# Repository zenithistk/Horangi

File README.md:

# Horangi

The Horangi is a split ergonomic keyboard with a row-staggered and curved layout.

* [horangi](/horangi) - Reversible with integrated trackball
* [horangi_grin](/horangi_grin) - Fully wireless and grin layout

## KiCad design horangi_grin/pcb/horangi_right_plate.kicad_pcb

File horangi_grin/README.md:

# Horangi_grin

The 'Horangi_grin' keyboard is a fully wireless, ergonomic split keyboard. Inspired by the [Grin layout keyboard](https://kbd.news/Grin-layout-1348.html), this keyboard features a layout similar to a 75% keyboard, making it easy for users accustomed to standard keyboards to adapt to a split keyboard. It can be used separately for each hand or combined as needed, and is designed to be as compact as possible, ensuring both practicality and portability.

* 83-key keyboard, grin layout
* XIAO ble MCU
* Fully wireless
* Hot-swap

## Build Guide (WIP)
* [Build Guide](BUILDGUIDE.md)

## Firmware
Only zmk firmware is available.
* [zmk firmware](firmware)
* [source code](https://github.com/zenithistk/zmk-config-horangi_grin)

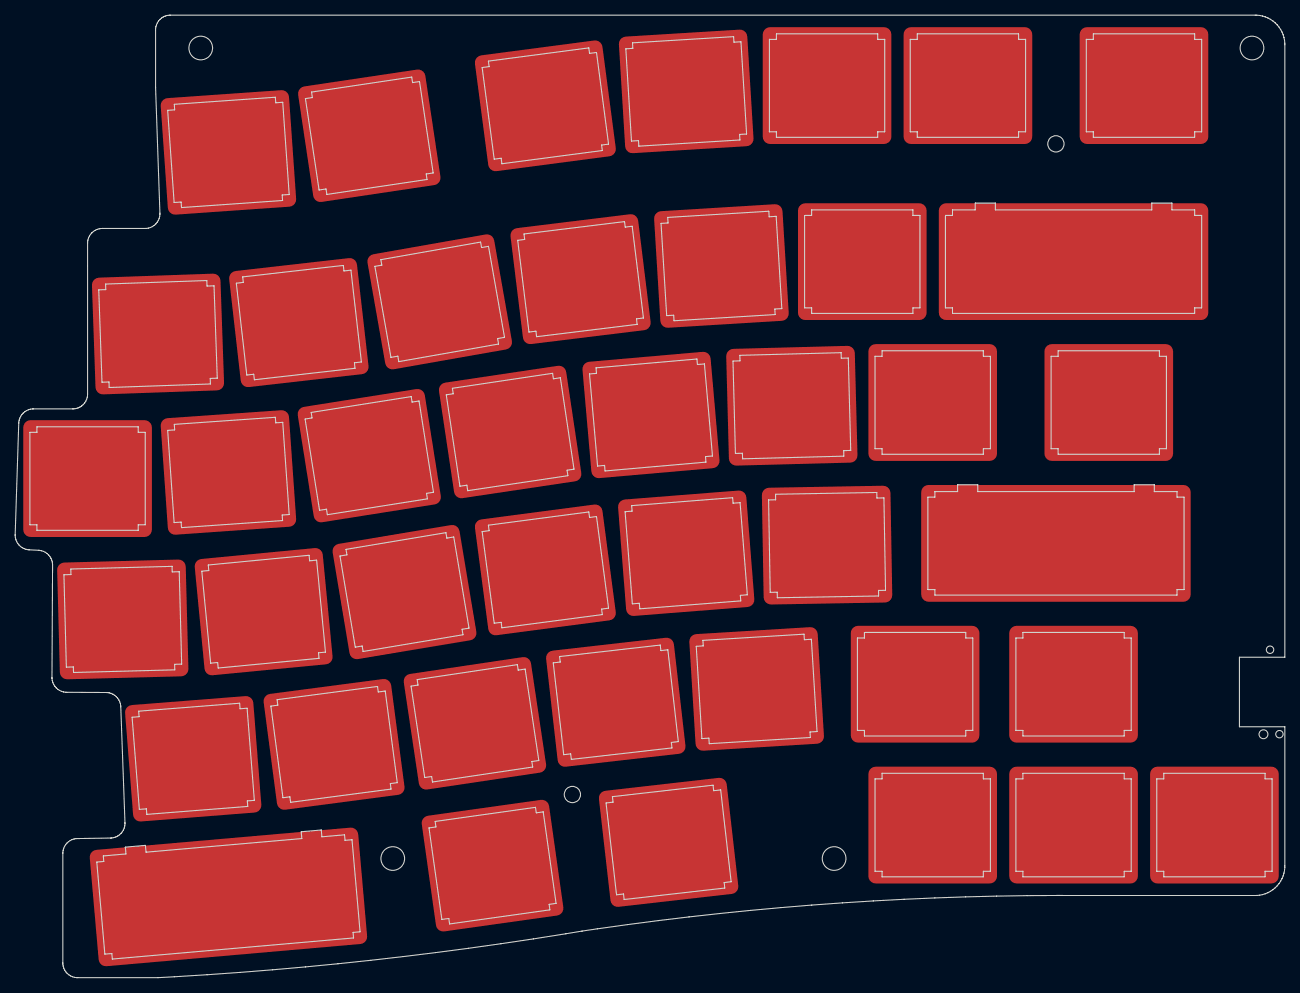
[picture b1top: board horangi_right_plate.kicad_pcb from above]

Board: 2 copper layers, 171.7 x 130.2 mm, 42 parts (0 on the bottom side), 7 nets, no tracks yet.

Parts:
SW1, SW2, SW3, SW4, SW5, SW6, SW7, SW8, SW9, SW10, SW11, SW12, SW13, SW15, SW16, SW17, SW18, SW19, SW20, SW21, SW22, SW23, SW24, SW25, SW26, SW27, SW28, SW29, SW30, SW31, SW32, SW33, SW34, SW37, SW38, SW39, SW40, SW41, SW42: Switch; MX-Alps_Switch_Cutout
SW14, SW35, SW36: Switch; MX-Alps_Switch_Cutout-1u_2u

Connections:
COL0: SW1.1 (COL), SW8.1 (COL), SW15.1 (COL), SW22.1 (COL), SW29.1 (COL), SW36.1 (COL)
COL1: SW2.1 (COL), SW9.1 (COL), SW16.1 (COL), SW23.1 (COL), SW30.1 (COL), SW37.1 (COL)
COL2: SW3.1 (COL), SW10.1 (COL), SW17.1 (COL), SW24.1 (COL), SW31.1 (COL), SW38.1 (COL)
COL3: SW4.1 (COL), SW11.1 (COL), SW18.1 (COL), SW25.1 (COL), SW32.1 (COL), SW39.1 (COL)
COL4: SW5.1 (COL), SW12.1 (COL), SW19.1 (COL), SW26.1 (COL), SW33.1 (COL), SW40.1 (COL)
COL5: SW6.1 (COL), SW13.1 (COL), SW20.1 (COL), SW27.1 (COL), SW34.1 (COL), SW41.1 (COL)
COL6: SW7.1 (COL), SW14.1 (COL), SW21.1 (COL), SW28.1 (COL), SW35.1 (COL), SW42.1 (COL)

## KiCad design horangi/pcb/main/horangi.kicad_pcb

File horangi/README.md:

# Horangi

The 'Horangi' keyboard is an ergonomic, symmetrical split keyboard with a built-in trackball. It utilizes Gateron KS-33 low profile switches and offers the option of hot-swapping. The MCU used is an rp2040 zero, contributing to a relatively small and aesthetically pleasing design. Additionally, it features m2 holes for tenting and supports the use of a trackball with additional parts.

Additionally, the Horangi features a very unique thumb cluster. It can be attached or detached as needed, and thanks to this special thumb cluster, it allows for the use of arrow keys, which are usually hard to find on typical split keyboards.

* 66-key layout, curved row stagger, arrow keys.
* rp2040-zero MCU
* Gateron low profile hot-swap
* Reversible pcb design
* Detachable thumb cluster
* Integrated trackball

## Keymap

## Build Guide (WIP)
* [Build Guide](BUILDGUIDE.md)

## Firmware
Only qmk firmware is available.
* [qmk firmware](firmware)
* [source code](https://github.com/zenithistk/qmk_firmware/tree/master/keyboards/horangi)

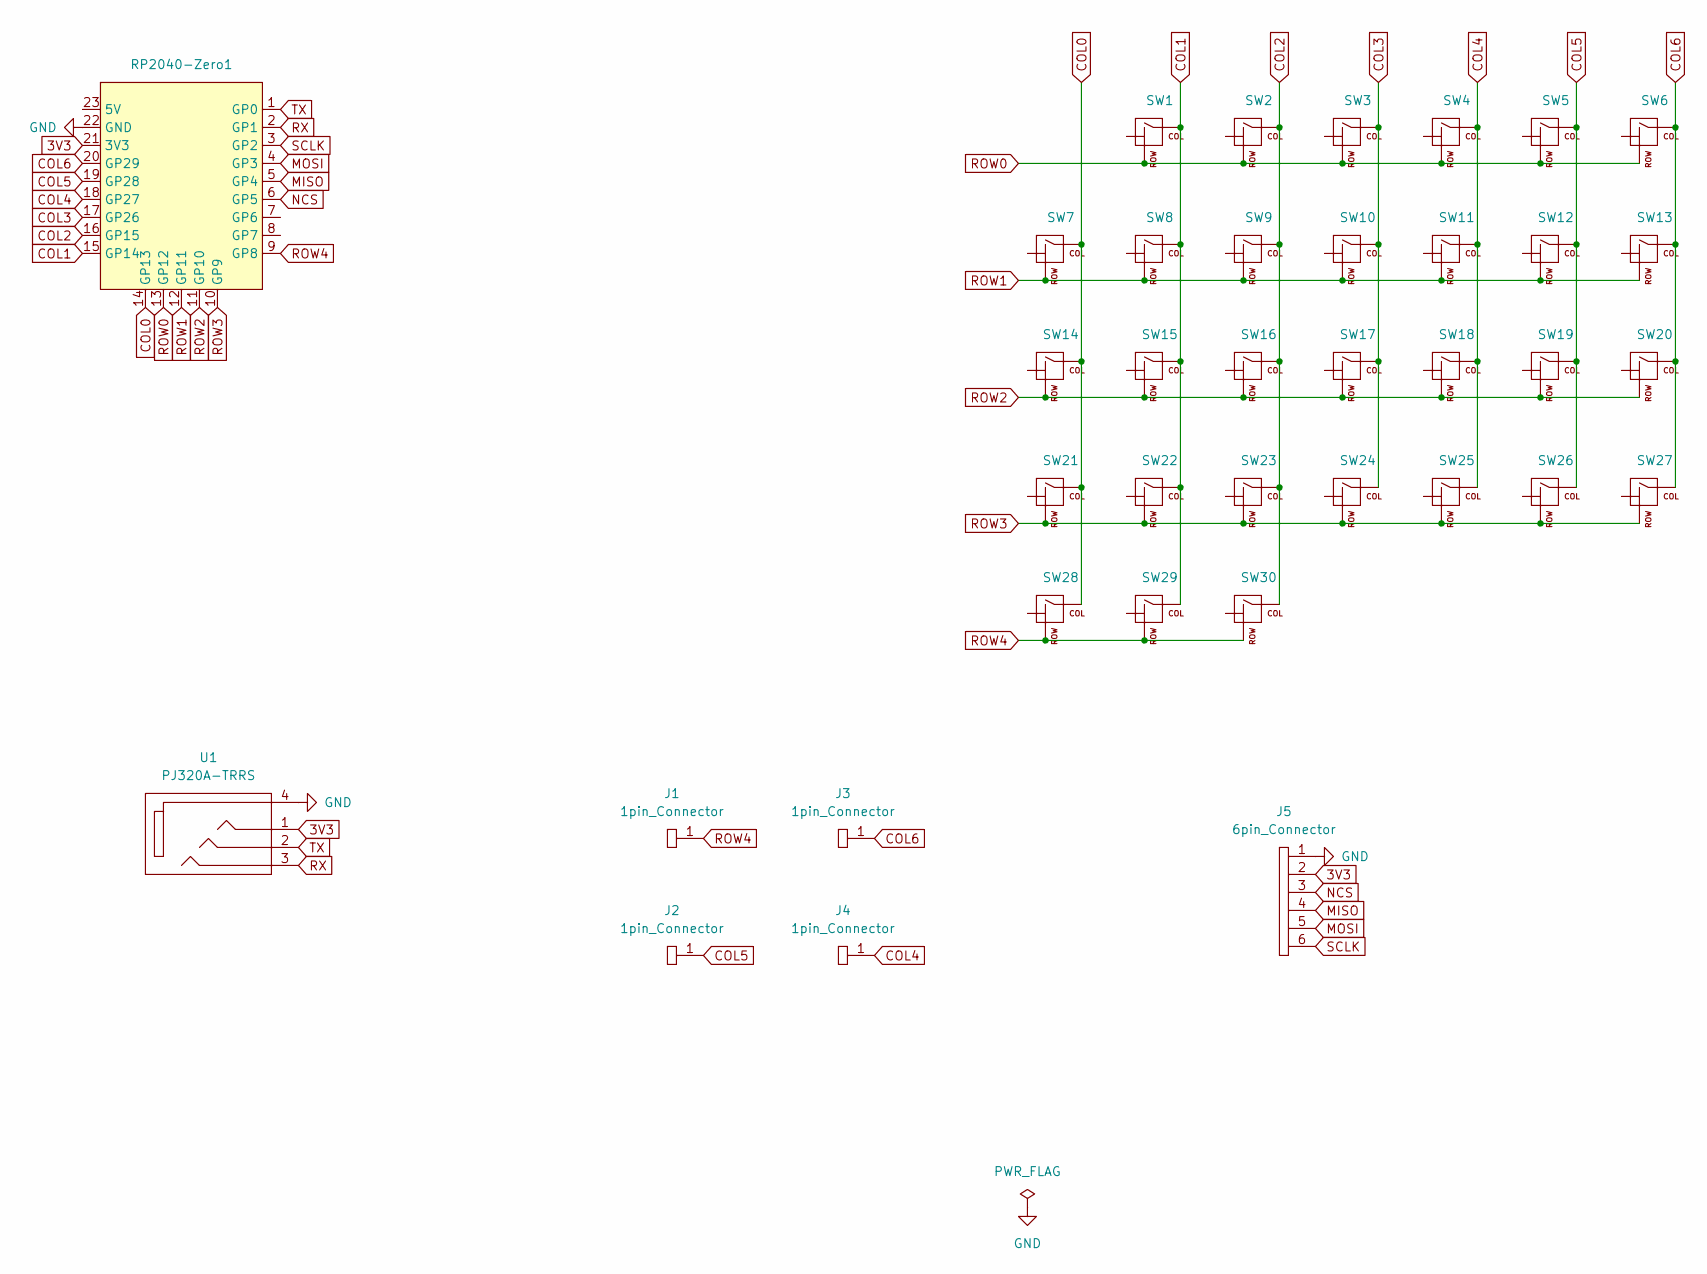
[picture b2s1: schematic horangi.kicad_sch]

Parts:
J1, J2, J3, J4: 1pin_Connector; 1pin_connector
J5: 6pin_Connector; 6pin_connector
RP2040-Zero1: RP2040-Zero
SW1, SW2, SW3, SW4, SW5, SW6, SW7, SW8, SW9, SW10, SW11, SW12, SW13, SW14, SW15, SW16, SW17, SW18, SW19, SW20, SW21, SW22, SW23, SW24, SW25, SW26, SW27, SW28, SW29, SW30: Switch; ks33-hotswap-diode-smd_1u
U1: PJ320A-TRRS; PJ320A-TRRS_reversable

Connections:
3V3: J5.2, RP2040-Zero1.21 (3V3), U1.1
COL0: RP2040-Zero1.14 (GP13), SW7.1 (COL), SW14.1 (COL), SW21.1 (COL), SW28.1 (COL)
COL1: RP2040-Zero1.15 (GP14), SW1.1 (COL), SW8.1 (COL), SW15.1 (COL), SW22.1 (COL), SW29.1 (COL)
COL2: RP2040-Zero1.16 (GP15), SW2.1 (COL), SW9.1 (COL), SW16.1 (COL), SW23.1 (COL), SW30.1 (COL)
COL3: RP2040-Zero1.17 (GP26), SW3.1 (COL), SW10.1 (COL), SW17.1 (COL), SW24.1 (COL)
COL4: J4.1, RP2040-Zero1.18 (GP27), SW4.1 (COL), SW11.1 (COL), SW18.1 (COL), SW25.1 (COL)
COL5: J2.1, RP2040-Zero1.19 (GP28), SW5.1 (COL), SW12.1 (COL), SW19.1 (COL), SW26.1 (COL)
COL6: J3.1, RP2040-Zero1.20 (GP29), SW6.1 (COL), SW13.1 (COL), SW20.1 (COL), SW27.1 (COL)
GND: J5.1, RP2040-Zero1.22 (GND), U1.4
MISO: J5.4, RP2040-Zero1.5 (GP4)
MOSI: J5.5, RP2040-Zero1.4 (GP3)
NCS: J5.3, RP2040-Zero1.6 (GP5)
ROW0: RP2040-Zero1.13 (GP12), SW1.2 (ROW), SW2.2 (ROW), SW3.2 (ROW), SW4.2 (ROW), SW5.2 (ROW), SW6.2 (ROW)
ROW1: RP2040-Zero1.12 (GP11), SW7.2 (ROW), SW8.2 (ROW), SW9.2 (ROW), SW10.2 (ROW), SW11.2 (ROW), SW12.2 (ROW), SW13.2 (ROW)
ROW2: RP2040-Zero1.11 (GP10), SW14.2 (ROW), SW15.2 (ROW), SW16.2 (ROW), SW17.2 (ROW), SW18.2 (ROW), SW19.2 (ROW), SW20.2 (ROW)
ROW3: RP2040-Zero1.10 (GP9), SW21.2 (ROW), SW22.2 (ROW), SW23.2 (ROW), SW24.2 (ROW), SW25.2 (ROW), SW26.2 (ROW), SW27.2 (ROW)
ROW4: J1.1, RP2040-Zero1.9 (GP8), SW28.2 (ROW), SW29.2 (ROW), SW30.2 (ROW)
RX: RP2040-Zero1.2 (GP1), U1.3
SCLK: J5.6, RP2040-Zero1.3 (GP2)
TX: RP2040-Zero1.1 (GP0), U1.2

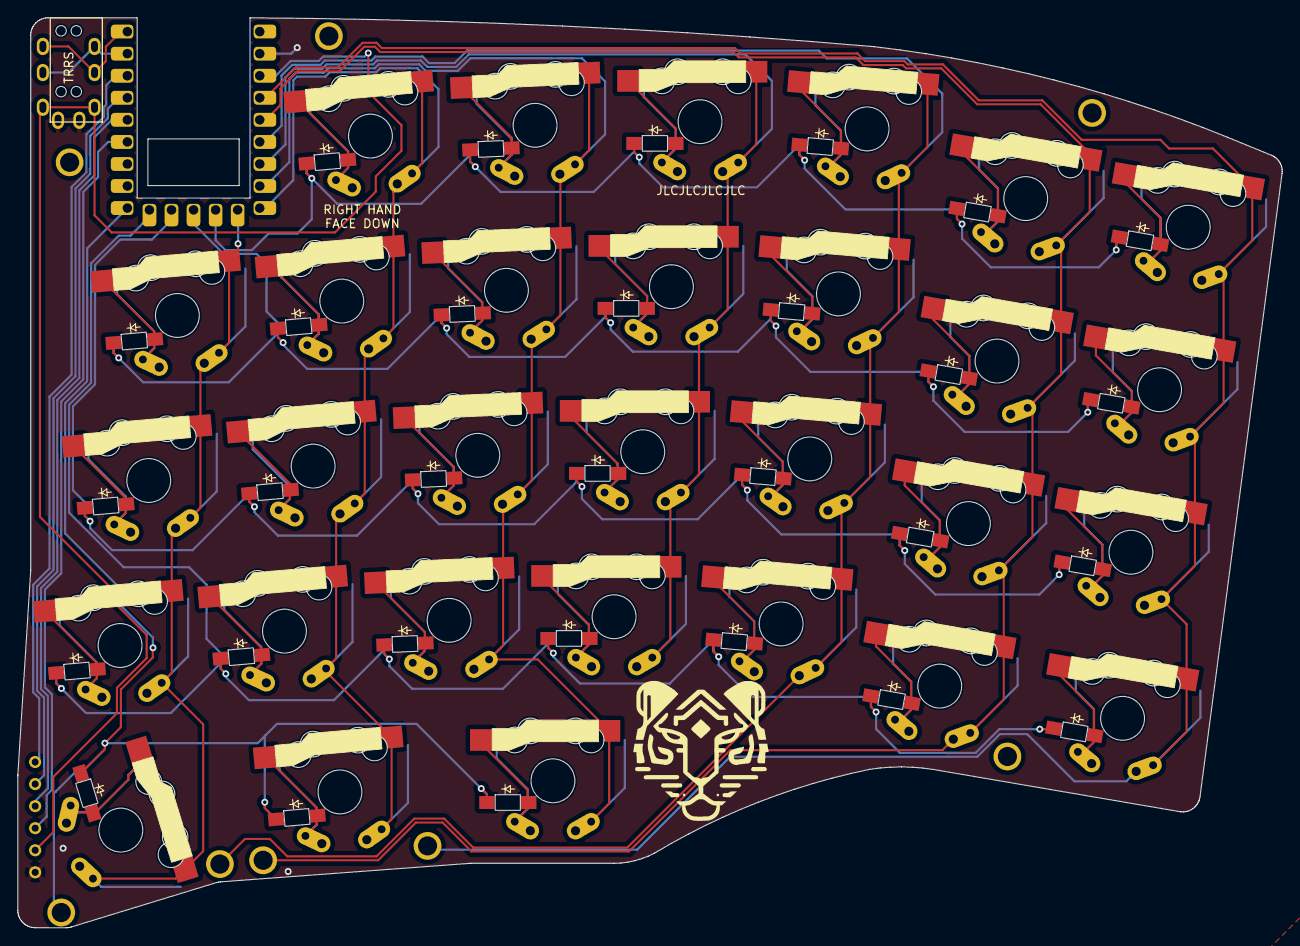
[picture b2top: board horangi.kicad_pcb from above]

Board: 2 copper layers, 145.6 x 104.7 mm, 41 parts (1 on the bottom side), 20 nets.

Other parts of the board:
TH1, TH1#2, TH1#3, TH1#4: HOLE; HOLE_M2

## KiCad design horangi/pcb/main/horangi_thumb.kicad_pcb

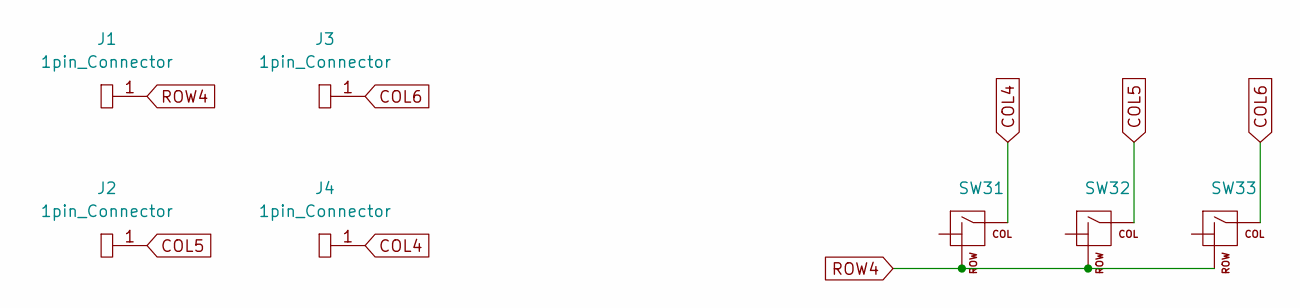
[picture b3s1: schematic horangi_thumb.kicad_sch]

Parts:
J1, J2, J3, J4: 1pin_Connector; 1pin_connector
SW31, SW32, SW33: Switch; ks33-hotswap-diode-smd_1u

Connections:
COL4: J4.1, SW31.1 (COL)
COL5: J2.1, SW32.1 (COL)
COL6: J3.1, SW33.1 (COL)
ROW4: J1.1, SW31.2 (ROW), SW32.2 (ROW), SW33.2 (ROW)

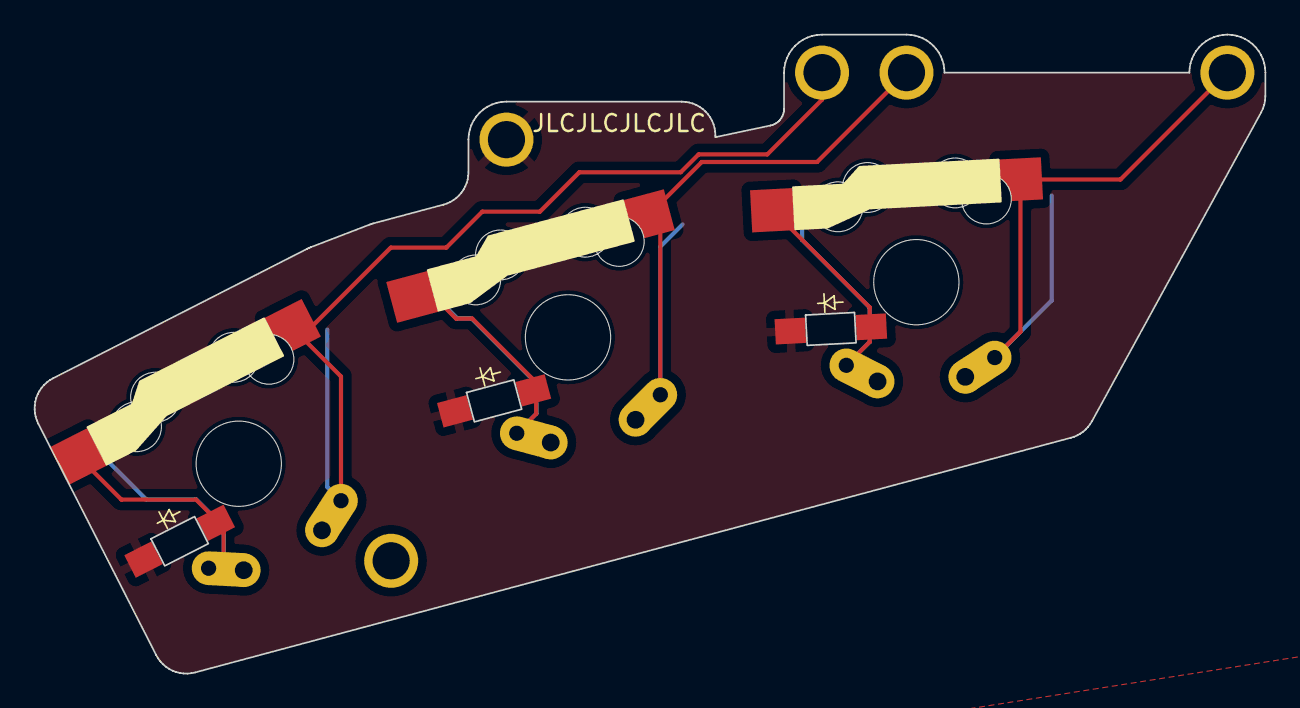
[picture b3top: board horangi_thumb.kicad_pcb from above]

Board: 2 copper layers, 72.9 x 37.8 mm, 7 parts (0 on the bottom side), 4 nets.

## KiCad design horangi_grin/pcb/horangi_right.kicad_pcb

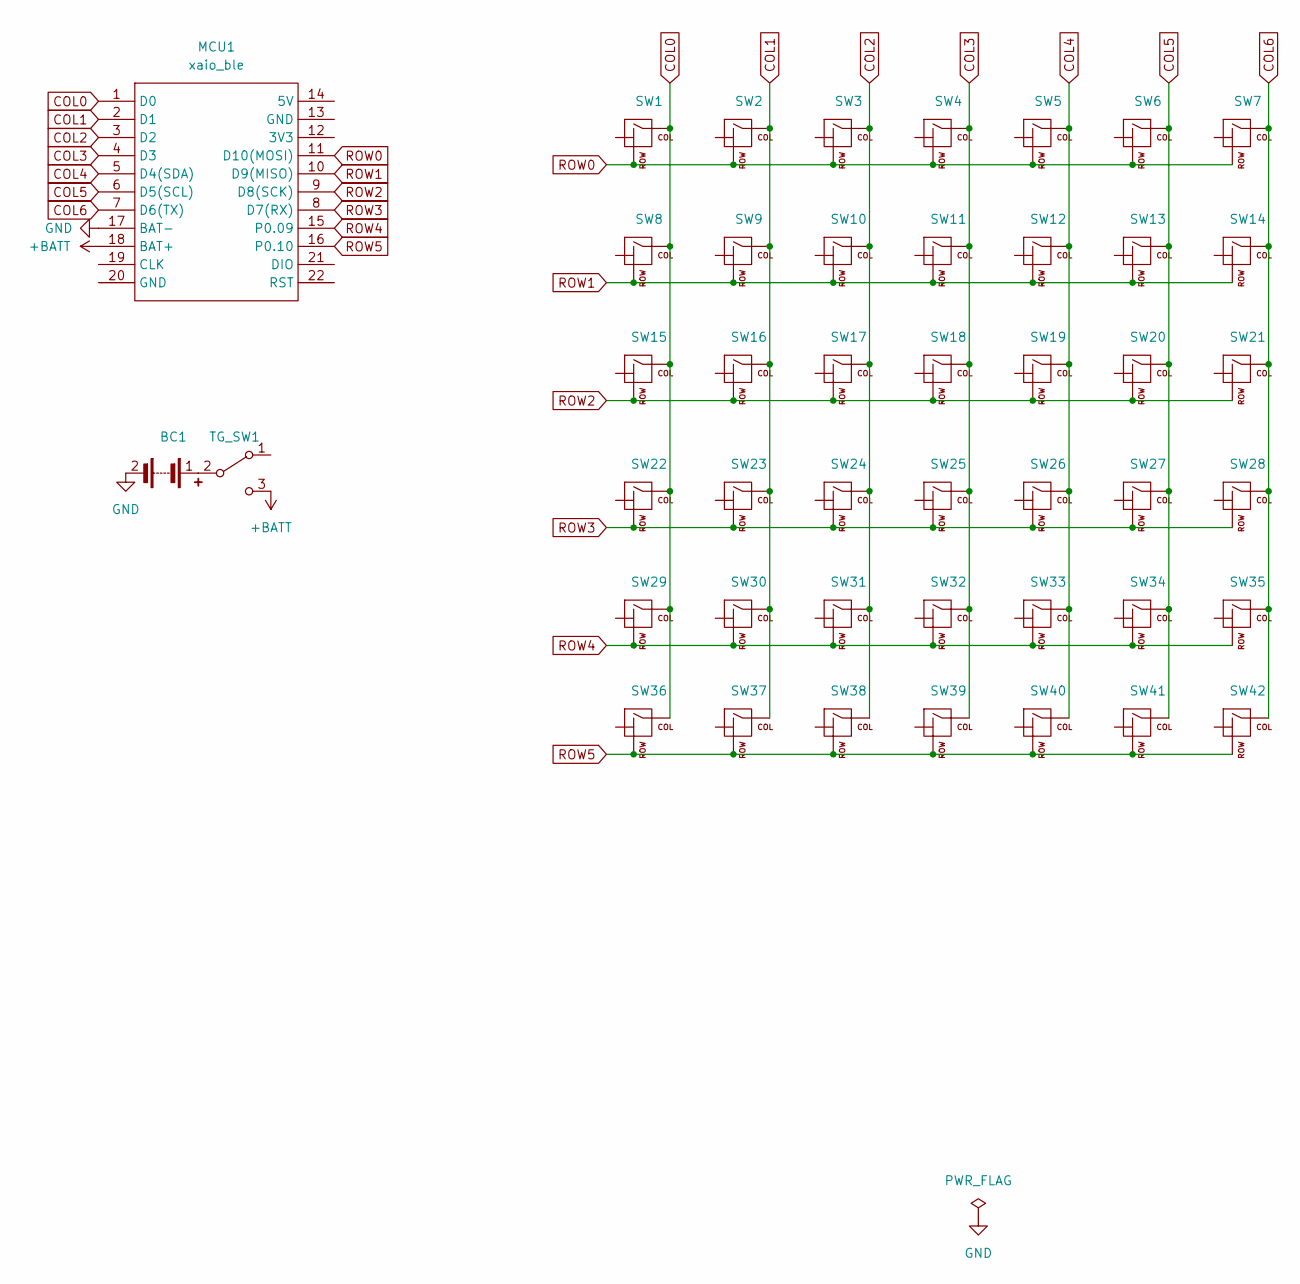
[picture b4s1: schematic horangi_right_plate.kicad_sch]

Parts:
BC1: Battery_Connector; battery_1.25mm_jst
MCU1: xaio_ble; Seeeduino XIAO-MOUDLE14P-2.54-21X17.8MM
SW1, SW2, SW3, SW4, SW5, SW6, SW7, SW8, SW9, SW10, SW11, SW12, SW13, SW14, SW15, SW16, SW17, SW18, SW19, SW20, SW21, SW22, SW23, SW24, SW25, SW26, SW27, SW28, SW29, SW30, SW31, SW32, SW33, SW34, SW35, SW36, SW37, SW38, SW39, SW40, SW41, SW42: Switch; MX-hotswap-diode-smd
TG_SW1: Toggle_Switch; SK19 toggle switch

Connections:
+BATT: MCU1.18 (BAT+), TG_SW1.3
COL0: MCU1.1 (D0), SW1.1 (COL), SW8.1 (COL), SW15.1 (COL), SW22.1 (COL), SW29.1 (COL), SW36.1 (COL)
COL1: MCU1.2 (D1), SW2.1 (COL), SW9.1 (COL), SW16.1 (COL), SW23.1 (COL), SW30.1 (COL), SW37.1 (COL)
COL2: MCU1.3 (D2), SW3.1 (COL), SW10.1 (COL), SW17.1 (COL), SW24.1 (COL), SW31.1 (COL), SW38.1 (COL)
COL3: MCU1.4 (D3), SW4.1 (COL), SW11.1 (COL), SW18.1 (COL), SW25.1 (COL), SW32.1 (COL), SW39.1 (COL)
COL4: MCU1.5 (D4(SDA)), SW5.1 (COL), SW12.1 (COL), SW19.1 (COL), SW26.1 (COL), SW33.1 (COL), SW40.1 (COL)
COL5: MCU1.6 (D5(SCL)), SW6.1 (COL), SW13.1 (COL), SW20.1 (COL), SW27.1 (COL), SW34.1 (COL), SW41.1 (COL)
COL6: MCU1.7 (D6(TX)), SW7.1 (COL), SW14.1 (COL), SW21.1 (COL), SW28.1 (COL), SW35.1 (COL), SW42.1 (COL)
GND: BC1.2, MCU1.17 (BAT-)
unnamed: BC1.1, TG_SW1.2
ROW0: MCU1.11 (D10(MOSI)), SW1.2 (ROW), SW2.2 (ROW), SW3.2 (ROW), SW4.2 (ROW), SW5.2 (ROW), SW6.2 (ROW), SW7.2 (ROW)
ROW1: MCU1.10 (D9(MISO)), SW8.2 (ROW), SW9.2 (ROW), SW10.2 (ROW), SW11.2 (ROW), SW12.2 (ROW), SW13.2 (ROW), SW14.2 (ROW)
ROW2: MCU1.9 (D8(SCK)), SW15.2 (ROW), SW16.2 (ROW), SW17.2 (ROW), SW18.2 (ROW), SW19.2 (ROW), SW20.2 (ROW), SW21.2 (ROW)
ROW3: MCU1.8 (D7(RX)), SW22.2 (ROW), SW23.2 (ROW), SW24.2 (ROW), SW25.2 (ROW), SW26.2 (ROW), SW27.2 (ROW), SW28.2 (ROW)
ROW4: MCU1.15 (P0.09), SW29.2 (ROW), SW30.2 (ROW), SW31.2 (ROW), SW32.2 (ROW), SW33.2 (ROW), SW34.2 (ROW), SW35.2 (ROW)
ROW5: MCU1.16 (P0.10), SW36.2 (ROW), SW37.2 (ROW), SW38.2 (ROW), SW39.2 (ROW), SW40.2 (ROW), SW41.2 (ROW), SW42.2 (ROW)

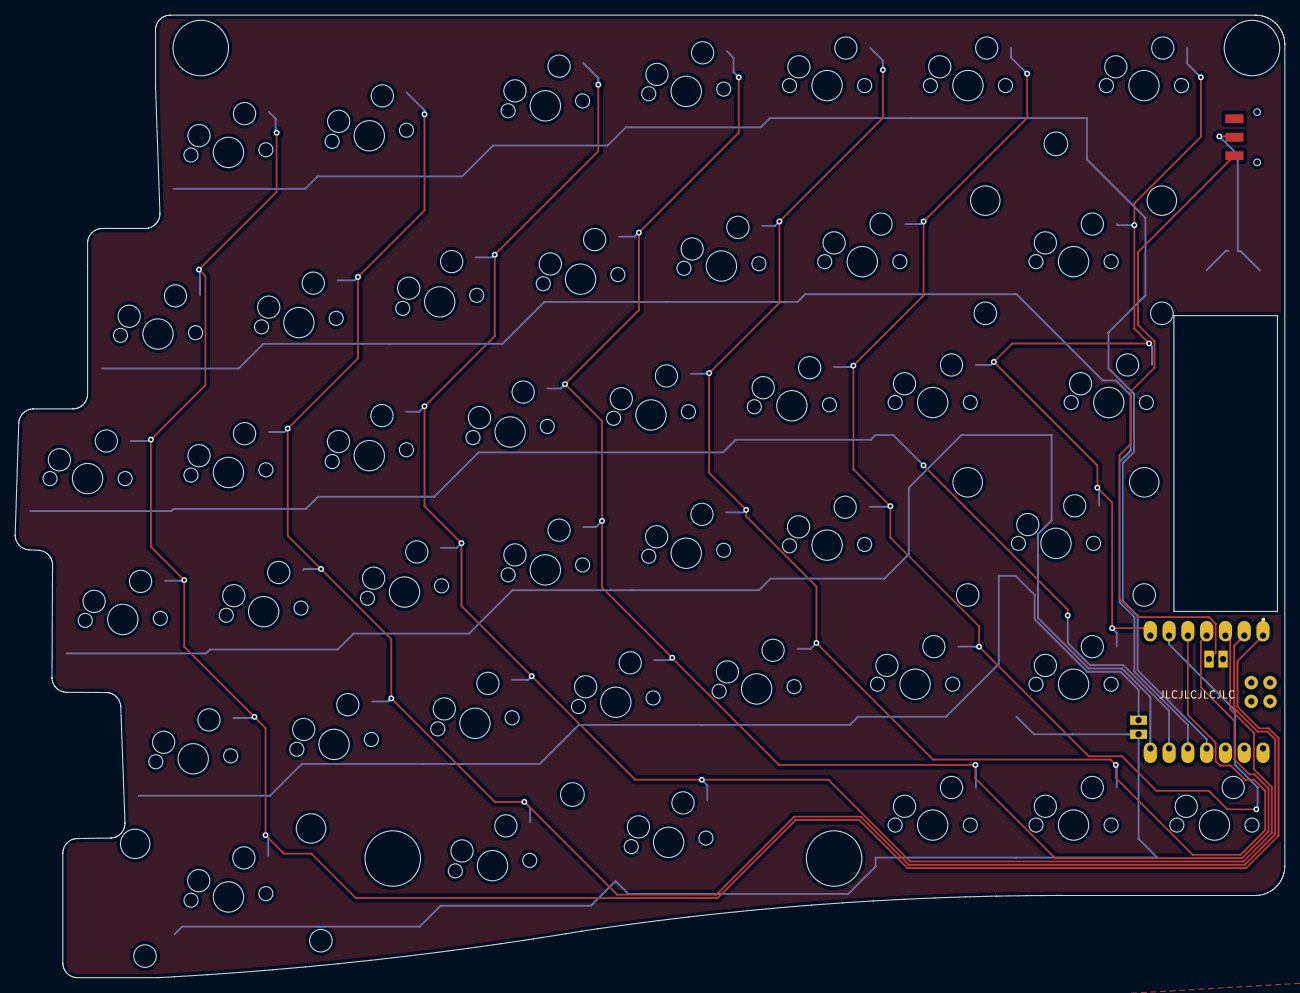
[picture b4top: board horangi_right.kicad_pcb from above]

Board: 2 copper layers, 171.7 x 130.2 mm, 45 parts (0 on the bottom side), 16 nets.

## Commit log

2023-12-27 upload horangi keyboard
2023-12-28 upload horangi_grin
2023-12-29 update horangi
2023-12-29 update build guide
